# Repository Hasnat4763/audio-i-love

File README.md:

# AudioCardio

AudioCardio is an Audio Card I designed which uses PCM2912A Audio IC to connect to your pc and use it as an audio Card

# Schematic

# PCB

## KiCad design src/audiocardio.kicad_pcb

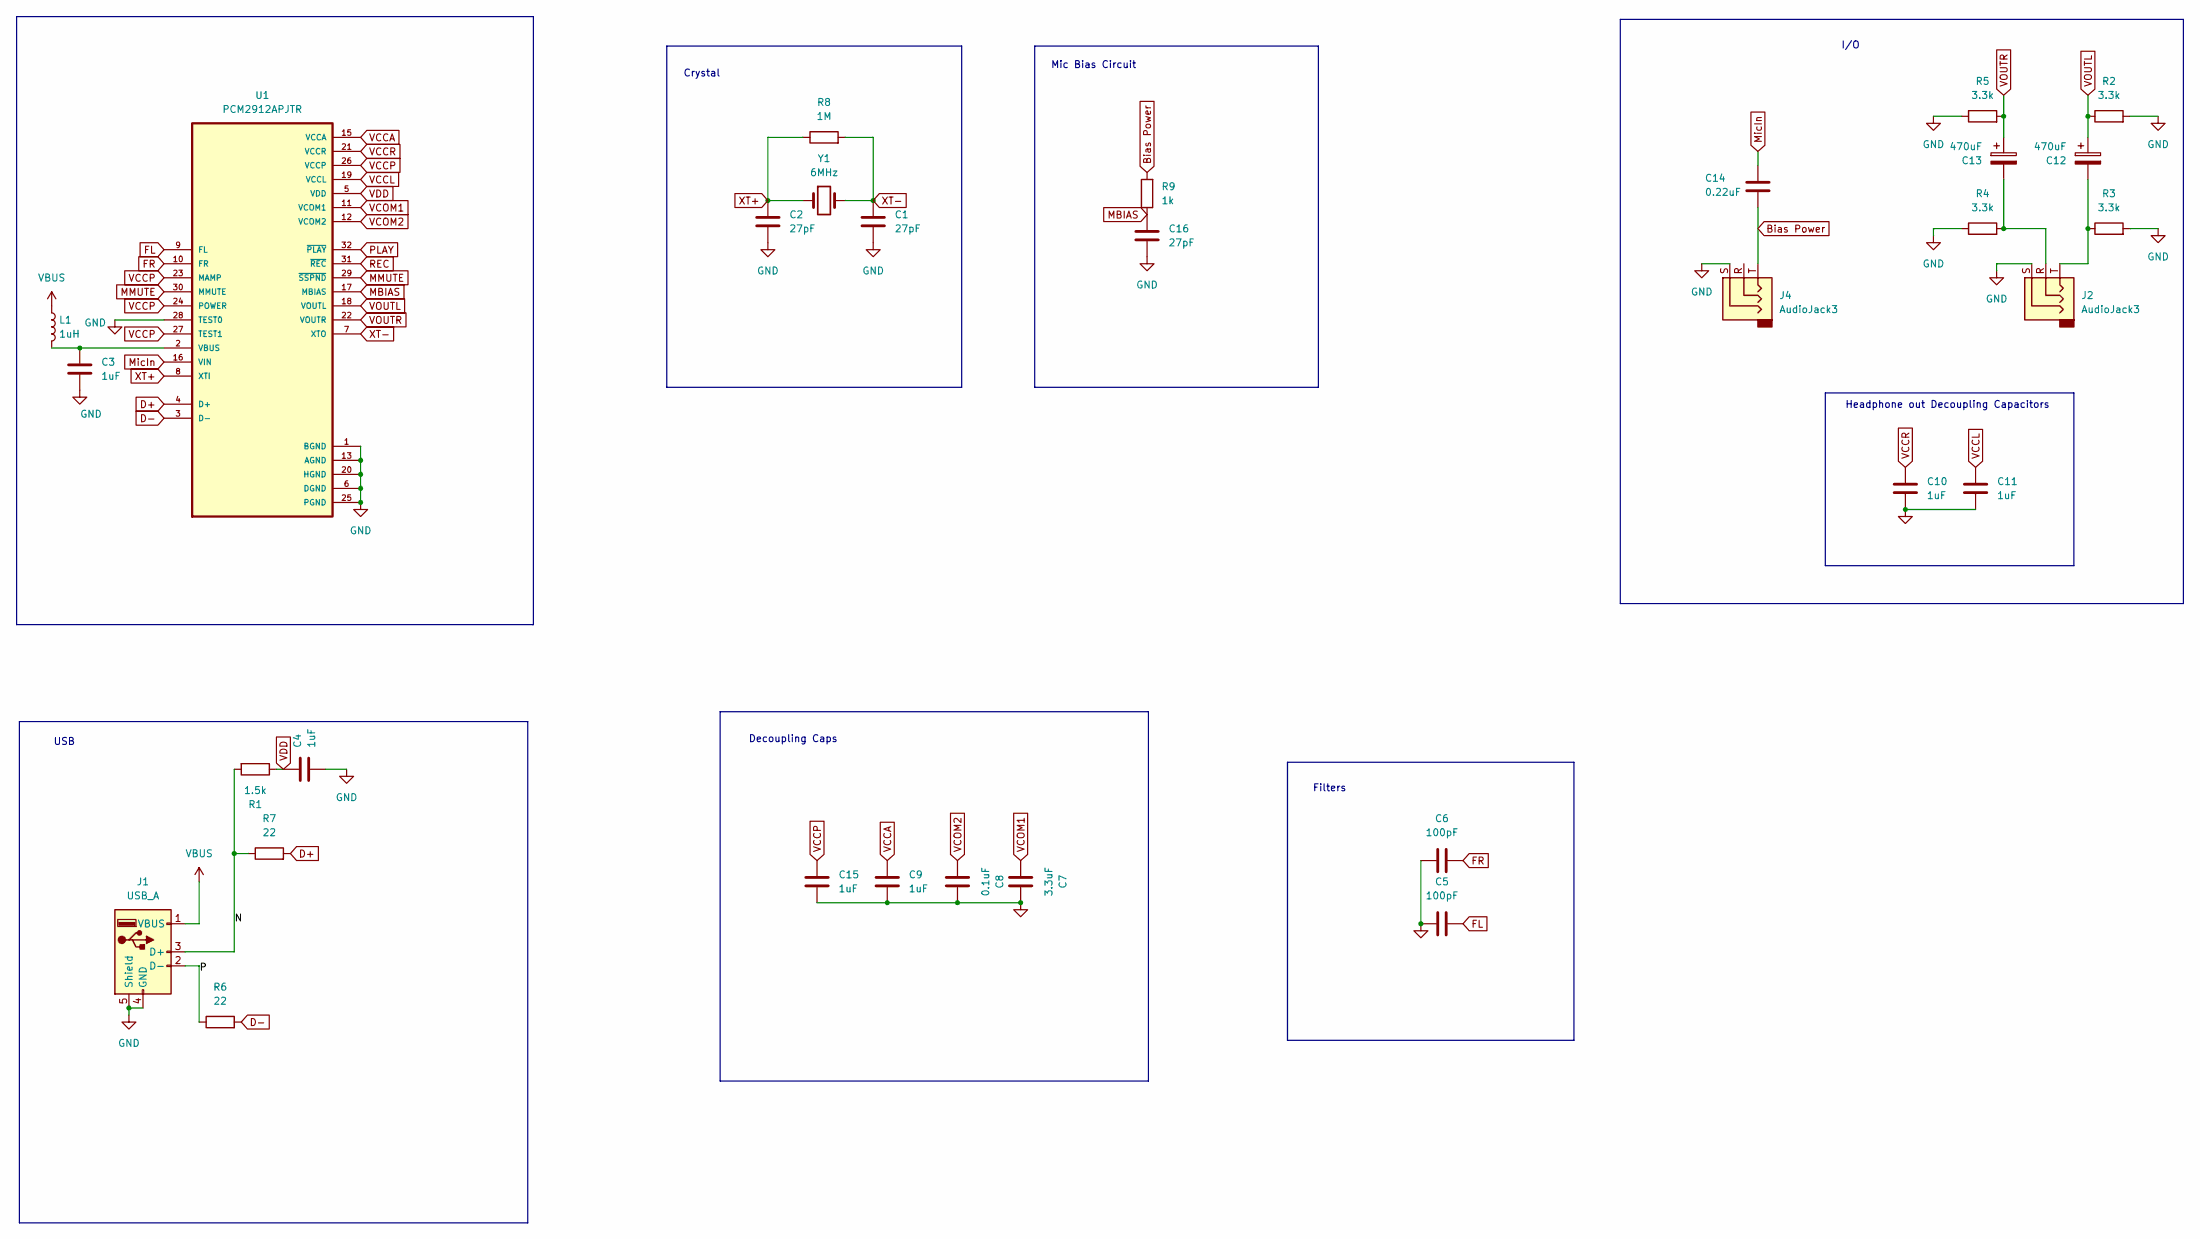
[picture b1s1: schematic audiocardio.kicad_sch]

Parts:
C1, C2, C16: 27pF; C_0603_1608Metric
C3, C4, C9, C10, C11, C15: 1uF; C_0603_1608Metric
C5, C6: 100pF; C_0603_1608Metric
C7: 3.3uF; C_Radial_D4.0mm_H5.0mm_P1.50mm
C8: 0.1uF; C_0603_1608Metric
C12, C13: 470uF; C_Radial_D4.0mm_H5.0mm_P1.50mm
C14: 0.22uF; C_Radial_D4.0mm_H5.0mm_P1.50mm
J1: USB_A; USB_A_Connfly_DS1098_Horizontal
J2, J4: AudioJack3; Jack_3.5mm_CUI_SJ1-3523N_Horizontal
L1: 1uH; L_0603_1608Metric
R1: 1.5k; R_Axial_DIN0204_L3.6mm_D1.6mm_P5.08mm_Horizontal
R2, R3, R4, R5: 3.3k; R_Axial_DIN0204_L3.6mm_D1.6mm_P5.08mm_Horizontal
R6, R7: 22; R_0603_1608Metric
R8: 1M; R_Axial_DIN0204_L3.6mm_D1.6mm_P5.08mm_Horizontal
R9: 1k; R_Axial_DIN0204_L3.6mm_D1.6mm_P5.08mm_Horizontal
U1: PCM2912APJTR; QFP80P900X900X120-32N
Y1: 6MHz; XTAL_ABLS-6.000MHz-20-B-3-H-T

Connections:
/N: J1.3 (D+), R1.2, R7.1
/P: J1.2 (D-), R6.1
Bias Power: C14.2, J4.T, R9.2
D+: R7.2, U1.4 (D+)
D-: R6.2, U1.3 (D-)
FL: C5.1, U1.9 (FL)
FR: C6.1, U1.10 (FR)
GND: C1.2, C2.2, C3.2, C4.2, C5.2, C6.2, C7.1, C8.1, C9.2, C10.2, C11.2, C15.2, C16.2, J1.4 (GND), J1.5 (Shield), J2.S, J4.S, R2.2, R3.2, R4.1, R5.1, U1.1 (BGND), U1.6 (DGND), U1.13 (AGND), U1.20 (HGND), U1.25 (PGND), U1.28 (TEST0)
MBIAS: C16.1, R9.1, U1.17 (MBIAS)
MMUTE: U1.29 (~SSPND), U1.30 (MMUTE)
MicIn: C14.1, U1.16 (VIN)
unnamed: C12.2, J2.T, R3.1
unnamed: C13.2, J2.R, R4.2
unnamed: C3.1, L1.2, U1.2 (VBUS)
PLAY: U1.32 (~PLAY)
REC: U1.31 (~REC)
VBUS: J1.1 (VBUS), L1.1
VCCA: C9.1, U1.15 (VCCA)
VCCL: C11.1, U1.19 (VCCL)
VCCP: C15.1, U1.23 (MAMP), U1.24 (POWER), U1.26 (VCCP), U1.27 (TEST1)
VCCR: C10.1, U1.21 (VCCR)
VCOM1: C7.2, U1.11 (VCOM1)
VCOM2: C8.2, U1.12 (VCOM2)
VDD: C4.1, R1.1, U1.5 (VDD)
VOUTL: C12.1, R2.1, U1.18 (VOUTL)
VOUTR: C13.1, R5.2, U1.22 (VOUTR)
XT+: C2.1, R8.1, U1.8 (XTI), Y1.1
XT-: C1.1, R8.2, U1.7 (XTO), Y1.2

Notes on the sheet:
I/O
Filters
Decoupling Caps
Mic Bias Circuit
USB
Headphone out Decoupling Capacitors
Crystal

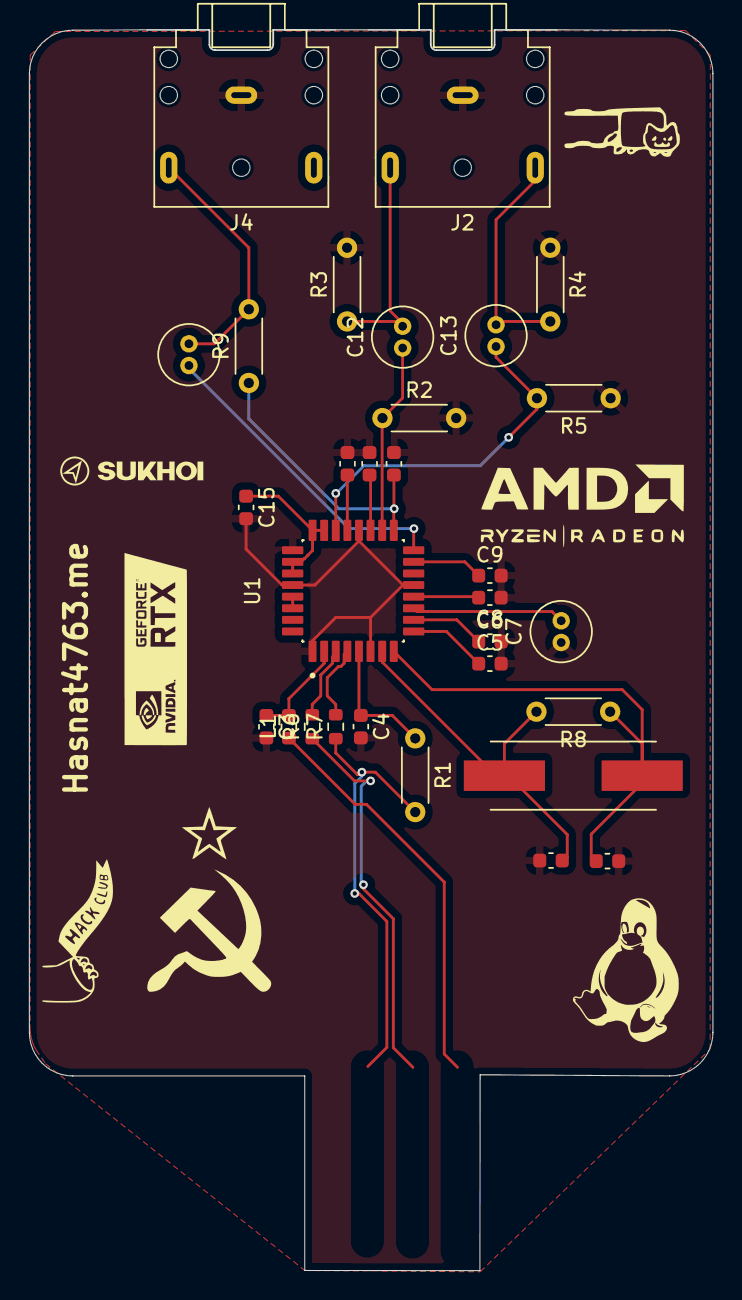
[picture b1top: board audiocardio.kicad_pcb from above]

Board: 2 copper layers, 47.1 x 85.5 mm, 30 parts (0 on the bottom side), 24 nets.

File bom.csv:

Designator,Footprint,Quantity,Value,LCSC Part #
"C1, C16, C2",0603,3,27pF,
"C10, C11, C15, C3, C4, C9",0603,6,1uF,
"C12, C13",C_Radial_D4.0mm_H5.0mm_P1.50mm,2,470uF,
C14,C_Radial_D4.0mm_H5.0mm_P1.50mm,1,0.22uF,
"C5, C6",0603,2,100pF,
C7,C_Radial_D4.0mm_H5.0mm_P1.50mm,1,3.3uF,
C8,0603,1,0.1uF,
"J2, J4",Jack_3.5mm_CUI_SJ1-3523N_Horizontal,2,AudioJack3,
L1,0603,1,1uH,
R1,R_Axial_DIN0204_L3.6mm_D1.6mm_P5.08mm_Horizontal,1,1.5k,
"R2, R3, R4, R5",R_Axial_DIN0204_L3.6mm_D1.6mm_P5.08mm_Horizontal,4,3.3k,
"R6, R7",0603,2,22,
R8,R_Axial_DIN0204_L3.6mm_D1.6mm_P5.08mm_Horizontal,1,1M,
R9,R_Axial_DIN0204_L3.6mm_D1.6mm_P5.08mm_Horizontal,1,1k,
U1,QFP80P900X900X120-32N,1,PCM2912APJTR,
Y1,XTAL_ABLS-6.000MHz-20-B-3-H-T,1,6MHz,

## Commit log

2025-08-18 Adding stuff
2025-09-10 changing stuff
